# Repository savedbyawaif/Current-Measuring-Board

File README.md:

This is an onboarding project I worked on for the University of Alberta EcoCar team.
The task is as follows:
"Design a current measuring board. This board will need to use a ATmega328P
microcontroller (same one used on Arduino UNO), to measure the current. The board
will be connected inline with the cable in which we are measuring the current. It will use
a hall current sensor (Allegro ACS723) to measure the current. The board will be
powered off a 9V battery, so a switching DC/DC regulator will be required to drop the
voltage from 9V to 5V, which the microcontroller requires. The board should have an
LCD or a 7-segment display which displays the current. The board should also have
USB functionality (enabled via wiring a USB to serial/TTL connector)."

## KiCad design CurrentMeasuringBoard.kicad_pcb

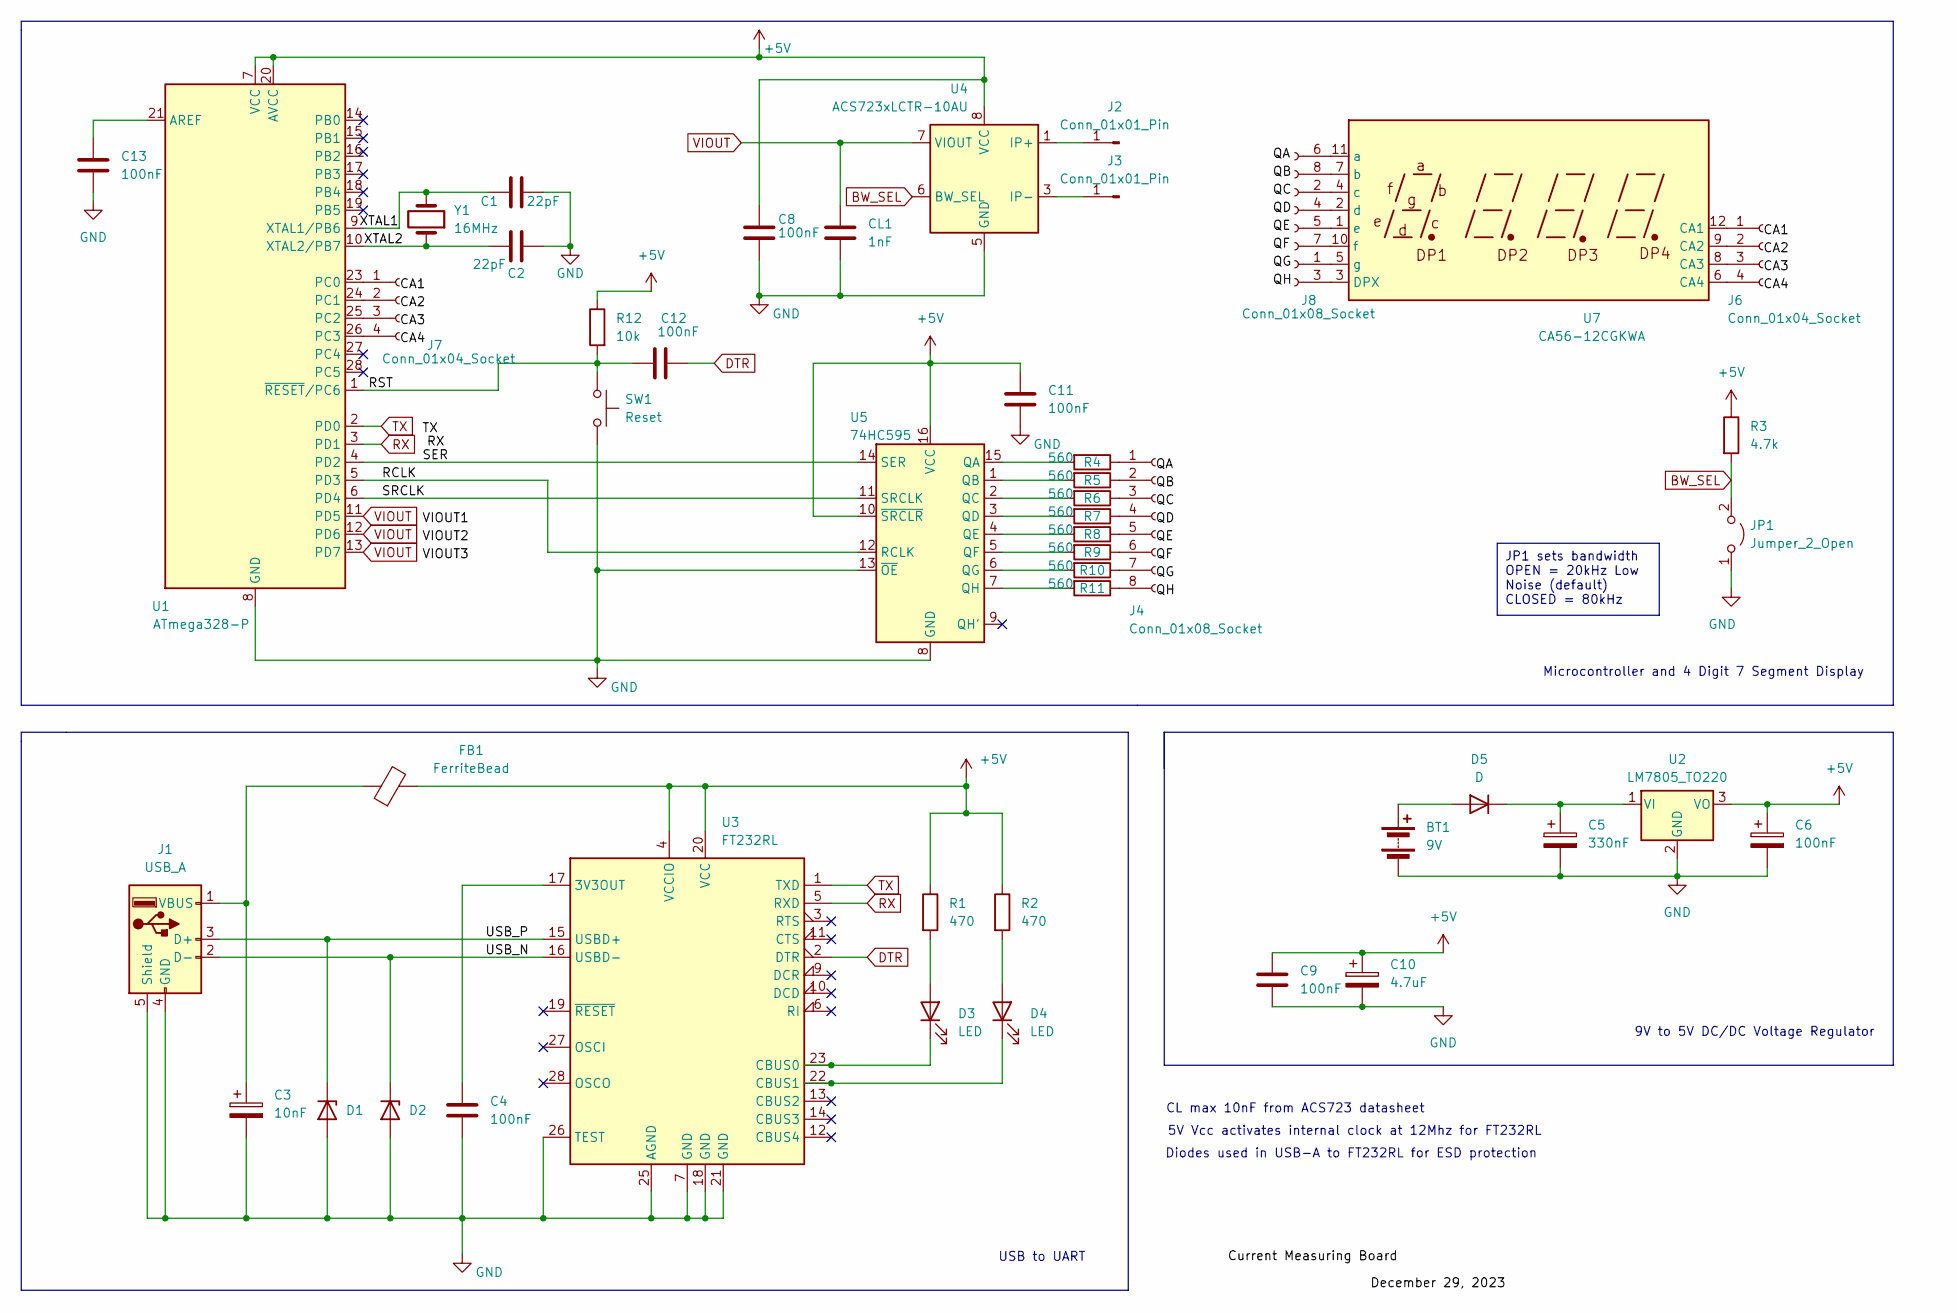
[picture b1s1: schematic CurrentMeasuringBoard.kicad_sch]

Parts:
BT1: 9V; PinHeader_1x02_P2.54mm_Horizontal
C1, C2: 22pF; C_0201_0603Metric
C3: 10nF; CP_EIA-2012-12_Kemet-R
C4, C8, C9, C11, C12, C13: 100nF; C_0402_1005Metric
C5: 330nF; CP_EIA-3216-12_Kemet-S
C6: 100nF; CP_EIA-3216-10_Kemet-I
C10: 4.7uF; CP_EIA-3528-12_Kemet-T
CL1: 1nF; C_0402_1005Metric
D1, D2: D_0402_1005Metric
D3, D4: LED; LED_0603_1608Metric
D5: D; D_0402_1005Metric
FB1: FerriteBead; L_0603_1608Metric
J1: USB_A; USB_A_Molex_48037-2200_Horizontal
J2, J3: Conn_01x01_Pin; PinHeader_1x01_P2.00mm_Vertical
J4, J8: Conn_01x08_Socket; PinSocket_1x08_P1.00mm_Vertical
J6, J7: Conn_01x04_Socket; PinSocket_1x04_P1.00mm_Vertical
JP1: Jumper_2_Open; SolderJumper-2_P1.3mm_Bridged2Bar_Pad1.0x1.5mm
R1, R2: 470; R_0402_1005Metric
R3: 4.7k; R_0402_1005Metric
R4, R5, R6, R7, R8, R9, R10, R11: 560; R_0402_1005Metric
R12: 10k; R_0402_1005Metric
SW1: Reset; SW_PUSH_6mm
U1: ATmega328-P; DIP-28_W7.62mm
U2: LM7805_TO220; TO-220-3_Vertical
U3: FT232RL; SSOP-28_5.3x10.2mm_P0.65mm
U4: ACS723xLCTR-10AU; SOIC-8_3.9x4.9mm_P1.27mm
U5: 74HC595; SOIC-16_3.9x9.9mm_P1.27mm
U7: CA56-12CGKWA
Y1: 16MHz; Crystal_SMD_5032-2Pin_5.0x3.2mm

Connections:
+5V: C6.1, C8.1, C9.1, C10.1, C11.1, FB1.2, R1.1, R2.1, R3.1, R12.1, U1.7 (VCC), U1.20 (AVCC), U2.3 (VO), U3.4 (VCCIO), U3.20 (VCC), U4.8 (VCC), U5.10 (~SRCLR), U5.16 (VCC)
/RCLK: U1.5 (PD3), U5.12 (RCLK)
/RST: C12.2, R12.2, SW1.2, U1.1 (~RESET/PC6)
/SER: U1.4 (PD2), U5.14 (SER)
/SRCLK: U1.6 (PD4), U5.11 (SRCLK)
/USB_N: D2.1 (K), J1.2 (D-), U3.16 (USBD-)
/USB_P: D1.1 (K), J1.3 (D+), U3.15 (USBD+)
/XTAL2: C2.2, U1.10 (XTAL2/PB7), Y1.1
BW_SEL: JP1.2 (B), R3.2, U4.6 (BW_SEL)
DTR: C12.1, U3.2 (DTR)
GND: BT1.2 (-), C1.1, C2.1, C3.2, C4.2, C5.2, C6.2, C8.2, C9.2, C10.2, C11.2, C13.2, CL1.2, D1.2 (A), D2.2 (A), J1.4 (GND), J1.5 (Shield), JP1.1 (A), SW1.1, U1.8 (GND), U1.22 (GND), U2.2 (GND), U3.7 (GND), U3.18 (GND), U3.21 (GND), U3.25 (AGND), U3.26 (TEST), U4.5 (GND), U5.8 (GND), U5.13 (~OE)
unnamed: BT1.1 (+), D5.2 (A)
unnamed: D3.2 (A), R1.2
unnamed: D3.1 (K), U3.23 (CBUS0)
unnamed: D4.2 (A), R2.2
unnamed: D4.1 (K), U3.22 (CBUS1)
unnamed: C5.1, D5.1 (K), U2.1 (VI)
unnamed: C3.1, FB1.1, J1.1 (VBUS)
unnamed: J2.1, U4.1 (IP+), U4.2 (IP+)
unnamed: J3.1, U4.3 (IP-), U4.4 (IP-)
unnamed: J4.1, R4.1
unnamed: J4.2, R5.1
unnamed: J4.3, R6.1
unnamed: J4.4, R7.1
unnamed: J4.5, R8.1
unnamed: J4.6, R9.1
unnamed: J4.7, R10.1
unnamed: J4.8, R11.1
unnamed: J6.1, U7.12 (CA1)
unnamed: J6.2, U7.9 (CA2)
unnamed: J6.3, U7.8 (CA3)
unnamed: J6.4, U7.6 (CA4)
unnamed: J7.1, U1.23 (PC0)
unnamed: J7.2, U1.24 (PC1)
unnamed: J7.3, U1.25 (PC2)
unnamed: J7.4, U1.26 (PC3)
unnamed: J8.1, U7.5 (g)
unnamed: J8.3, U7.3 (DPX)
unnamed: J8.5, U7.1 (e)
unnamed: J8.6, U7.11 (a)
unnamed: J8.7, U7.10 (f)
unnamed: J8.8, U7.7 (b)
unnamed: C13.1, U1.21 (AREF)
unnamed: C1.2, U1.9 (XTAL1/PB6), Y1.2
unnamed: C4.1, U3.17 (3V3OUT)
unnamed: R4.2, U5.15 (QA)
unnamed: R5.2, U5.1 (QB)
unnamed: R6.2, U5.2 (QC)
unnamed: R7.2, U5.3 (QD)
unnamed: R8.2, U5.4 (QE)
unnamed: R9.2, U5.5 (QF)
unnamed: R10.2, U5.6 (QG)
unnamed: R11.2, U5.7 (QH)
unnamed: J8.2 (Pin_4), U7.4 (c)
unnamed: J8.4, U7.2 (d)
RX: U1.3 (PD1), U3.5 (RXD)
TX: U1.2 (PD0), U3.1 (TXD)
VIOUT: CL1.1, U1.11 (PD5), U1.12 (PD6), U1.13 (PD7), U4.7 (VIOUT)

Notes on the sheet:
JP1 sets bandwidth OPEN = 20kHz Low Noise (default) CLOSED = 80kHz
CL max 10nF from ACS723 datasheet
USB to UART
Microcontroller and 4 Digit 7 Segment Display
9V to 5V DC/DC Voltage Regulator
Diodes used in USB-A to FT232RL for ESD protection
5V Vcc activates internal clock at 12Mhz for FT232RL

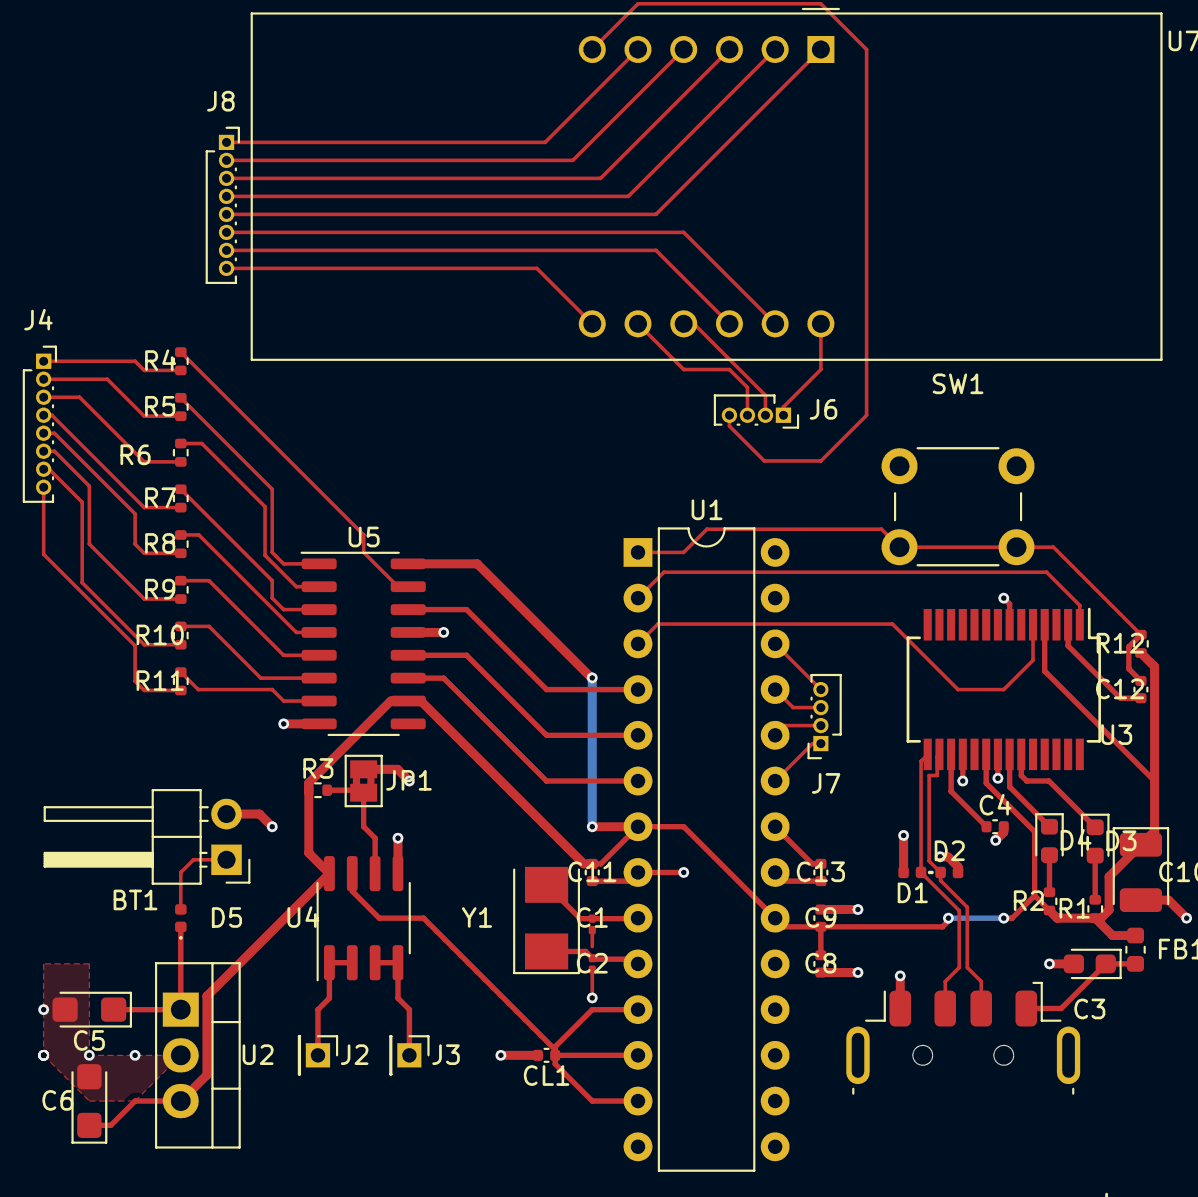
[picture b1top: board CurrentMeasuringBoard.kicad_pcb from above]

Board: 2 copper layers, 48 parts (0 on the bottom side), 58 nets.

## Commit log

2024-01-03 Add Schematic and PCB files
    Current Measuring Board Project
